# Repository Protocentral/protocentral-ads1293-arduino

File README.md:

# ProtoCentral ADS1293 ECG Arduino Library

Arduino library for the **ProtoCentral ADS1293 Breakout**: 3-lead and 5-lead ECG from the TI ADS1293 three-channel 24-bit analog front end. It exposes every feature of the chip, from lead-off detection and pace channels to the Wilson terminal and battery monitor, and runs on an Arduino Uno.

## Don't have one? [Buy it here](https://protocentral.com/product/protocentral-ads1293-breakout-board/)

## Links

| | |
|---|---|
| Product page | https://protocentral.com/product/protocentral-ads1293-breakout-board/ |
| Getting started guide (pinout, electrodes, OpenView) | https://protocentral.com/product/protocentral-ads1293-breakout-board/docs/getting-started/ |
| Hardware design files | https://github.com/Protocentral/protocentral_ads1293 |
| OpenView companion app | https://github.com/Protocentral/protocentral_openview |
| ADS1293 datasheet (TI SNAS602C) | https://www.ti.com/lit/ds/symlink/ads1293.pdf |

## How it works

The ADS1293 has three measurement channels, each with an instrumentation amplifier (fixed gain 3.5), a sigma-delta modulator and a digital filter. A switch matrix connects any of its six inputs to any channel. The library's lead sets use the breakout's electrode wiring:

| Channel | 3-lead | 5-lead |
|---|---|---|
| **CH1** | Lead I = LA − RA | Lead I = LA − RA |
| **CH2** | Lead II = LL − RA | Lead II = LL − RA |
| **CH3** | off | V1 − WCT (Wilson central terminal, built on-chip from RA, LA and LL) |

The right-leg drive holds the body at mid-supply through the RL electrode and cancels common-mode noise. Lead III = II − I.

## Features

- 3-lead and 5-lead ECG at 25–1600 SPS (up to 6.4 kSPS per channel), with any input-to-channel routing
- Lead-off detection: DC, analog AC and digital AC
- Digital pace data at up to 25.6 kSPS, and the analog pace channel
- Self-test signals, supply-voltage monitor and every error register
- Multi-board operation with a shared clock and SYNCB
- Polled, interrupt-driven, or no DRDY pin at all; readings converted to µV
- No dependencies. Runs on AVR, Uno R4, Nano 33 BLE, nRF52840, ESP32 (also S2/S3/C3) and RP2040

> **Not a medical device. For research and education only.** The breakout has no patient isolation: power the host from a battery when electrodes are on a person.

## Installation

- **Arduino Library Manager (recommended):** search for **ProtoCentral ADS1293** and install **ProtoCentral ADS1293 ECG Library**.
- **Manual:** download this repository as a ZIP, then use **Sketch → Include Library → Add .ZIP Library…**

## Wiring

The board pinout, electrode placement and power options are in the [getting started guide](https://protocentral.com/product/protocentral-ads1293-breakout-board/docs/getting-started/). The examples use each board's default SPI pins (SCK, MISO, MOSI) plus these:

| Breakout | Uno / Nano / R4 | ESP32 | ESP32-S2 / S3 | ESP32-C3 |
|---|---|---|---|---|
| CSB  | D4 | GPIO5 (SS) | SS (GPIO10 on S3) | GPIO7 (SS) |
| DRDY | D2 | GPIO4  | GPIO4 | GPIO3 |
| RST  | D5 | GPIO25 | GPIO5 | GPIO1 |
| SYNC | D6 | GPIO26 | GPIO6 | GPIO10 |

**Wire RST and SYNC to the MCU.** On the v2 board they reach the chip through a level shifter, with no pull-up on the header side. Connect both to MCU pins and pass those pins to the constructor; the library then holds them in a defined state. An RST or SYNC pin that is left undriven can stop conversions. (v1 boards have no SYNC pin: pass `-1` for it.)

Power the board from your MCU's I/O voltage: the header's logic level equals VCC.

## Quick Start

```cpp
#include <SPI.h>
#include "Protocentral_ADS1293.h"

Protocentral_ADS1293 ads(4 /*CS*/, 2 /*DRDY*/, 5 /*RST*/, 6 /*SYNC*/);

void setup() {
    Serial.begin(115200);
    if (!ads.begin()) {                        // 3-lead ECG at 200 SPS
        Serial.println((int)ads.lastError());  // see ADS1293_Status
        while (1);
    }
}

void loop() {
    ADS1293_Sample s;
    if (ads.available() && ads.read(s)) {
        Serial.print(ads.countsToMicrovolts(s.ecg[0]));  // Lead I, µV
        Serial.print(' ');
        Serial.println(ads.countsToMicrovolts(s.ecg[1], ADS1293_Channel::CH2));  // Lead II
    }
}
```

### Configuration

`begin()` with no arguments sets up 3-lead ECG at 200 SPS from the on-board crystal, with right-leg drive and DC lead-off detection. Pass an `ADS1293_Config` to change it:

```cpp
ADS1293_Config cfg;
cfg.leadSet  = ADS1293_LeadSet::FiveLead;   // ThreeLead, FiveLead or Custom
cfg.dataRate = ADS1293_DataRate::SPS_400;   // SPS_25 ... SPS_1600
cfg.leadOff  = false;
cfg.sync     = ADS1293_SyncMode::Auto;      // Master / Slave for multi-board sync
ads.begin(cfg);
```

The other fields (clock source, high-resolution mode, test signal, ...) are documented in `Protocentral_ADS1293.h`. Every setter also works later, while streaming.

Any `SPIClass` and any pin can be used: `Protocentral_ADS1293 ads(CS, DRDY, RST, SYNC, SPI1);`, with `-1` for pins that are not wired. On ESP32, `ads.begin(sck, miso, mosi)` selects custom SPI pins.

## Data format

`read()` fills an `ADS1293_Sample`:

| Field | Meaning |
|---|---|
| `ecg[3]` | ECG counts per channel, signed around mid-scale (0 = 0 V differential) |
| `pace[3]` | Pace counts (channels with pace read-back only) |
| `ecgUpdated` / `paceUpdated` | Bit *n* set: channel *n*+1 has a new conversion |
| `leadOff` | Lead-off flags (`ADS1293_ELECTRODE_RA` …), read while an alarm is active |
| `errors` | Error flags (`ADS1293_ERR_*`), read while an alarm is active |

`countsToMicrovolts(counts, channel)` converts to µV at the electrodes, using the full-scale code for the channel's current filter settings. The input range is ±400 mV differential.

## API Reference

| Method | Description |
|---|---|
| `Protocentral_ADS1293(cs, drdy = -1, reset = -1, sync = -1, SPIClass& spi = SPI)` | `-1` = pin not wired |
| `bool begin()` / `begin(const ADS1293_Config&)` | Reset, check the chip, configure, start and verify conversions |
| `ADS1293_Status lastError()` | `Ok`, `SpiError`, `WrongChipId`, `VerifyFailed`, `NoClock`, `Timeout`, ... |
| `bool available()` / `bool read(ADS1293_Sample&)` | New data is waiting / read it |
| `enableDataReadyInterrupt()` / `missedSamples()` | Latch DRDY with an interrupt / count overwritten samples |
| `dataReadyPinFault()` | True when DRDY did not follow the chip and the driver switched to polling |
| `reset()` / `end()` | Reset and re-apply the configuration / power down |
| `float countsToMicrovolts(counts, ch)` | Units |

The full feature API, grouped as in `Protocentral_ADS1293.h`, where each method is documented:

| Area | Methods |
|---|---|
| Conversion and power | `start`, `stop`, `standby`, `powerDown`, `wakeup` |
| Data rate and filters | `setDataRate`, `setR2`, `setR3`, `setDoublePaceRate`, `setHighSampleClock`, `setEcgFilterBypass`, `getSampleRate`, `getPaceRate` |
| Read-back and DRDY | `setEcgReadback`, `setPaceReadback`, `setDataReadySource`, `setDataReadyMasking` |
| Channels | `setChannelInputs`, `setChannelEnabled`, `setTestSignal`, `setHighResolution`, `setFaultDetection` |
| Lead-off | `configureLeadOffDC`, `configureLeadOffAnalogAC`, `configureLeadOffDigitalAC`, `disableLeadOff`, `readLeadOffStatus` |
| Patient reference | `configureCommonModeDetect`, `configureRLD`, `configureWilson`, `configureGoldberger`, `setReference` |
| Pace, clock, sync | `configureAnalogPace`, `setClockOutput`, `setSyncMode`, `configureSync`, `setDriveStrength` |
| Errors and monitoring | `readErrorStatus`, `readRangeErrors`, `readSyncErrors`, `readMiscErrors`, `setAlarmMask`, `setAlarmFilter`, `readSupplyVoltage` |
| Registers | `readRegister`, `writeRegister`, `printRegisters` |

## Examples

| # | Sketch | Description |
|---|---|---|
| 01 | `01.ThreeLeadSerialPlotter` | Leads I, II and III in µV in the Arduino Serial Plotter |
| 02 | `02.FiveLeadSerialPlotter` | Leads I, II and V1 (Wilson central terminal) |
| 03 | `03.OpenView` | Stream three leads to [OpenView](https://github.com/Protocentral/protocentral_openview) |
| 04 | `04.LeadOffDetection` | Report which electrode is off, DC or analog AC mode |
| 05 | `05.SelfTest` | Test signals and noise floor on all channels, no electrodes needed |
| 06 | `06.InterruptDriven` | 400 SPS with an interrupt on DRDY and a missed-sample counter |
| 07 | `07.PaceDetection` | 3.2 kSPS pace data and a simple pacemaker-pulse detector |
| 08 | `08.SupplyAndAlarms` | Supply voltage and every error register, decoded |
| 09 | `09.MultiBoardClockSync` | Two boards sharing clock and SYNCB: six ECG channels sampled in step |
| 10 | `10.Diagnostics` | Register dump plus clock, data-path, DRDY and signal-chain checks. **Run this first if something is wrong** |

All examples print at 115200 baud.

## Troubleshooting

Run `10.Diagnostics` first; it reports which stage fails.

- **`SpiError`:** check the CSB/SCK/MOSI/MISO wiring, VCC and GND. On ESP32-S2/S3/C3, do not use pins 18/19/23.
- **`VerifyFailed`:** registers do not read back correctly. Shorten the wires, or define `ADS1293_SPI_CLOCK 500000` before the include.
- **`NoClock`, or data that comes and goes between resets:** check that RST and SYNC are wired to the pins passed to the constructor (see Wiring), then power-cycle the board, not only the MCU.
- **DRDY stuck:** remove any pull-up or pull-down from DRDY. The library notices a DRDY pin that does not follow the chip and polls instead (`dataReadyPinFault()` returns true); `10.Diagnostics` reports it.

Electrode and signal-quality problems are covered in the [getting started guide](https://protocentral.com/product/protocentral-ads1293-breakout-board/docs/getting-started/).

## Migrating from 1.x

Version 2.0 is a ground-up rewrite; see [CHANGELOG.md](CHANGELOG.md).

| 1.x | 2.0 |
|---|---|
| `#include "protocentral_ads1293.h"` | `#include "Protocentral_ADS1293.h"` |
| `ads1293 ADS1293(DRDY, CS);` | `Protocentral_ADS1293 ads(CS, DRDY, RST, SYNC);` (note the order) |
| `begin()` + ten `configure…()` calls | `ads.begin()` or `ads.begin(cfg)`, which returns `bool` |
| `configureChannel3(...)` + `configureWilsonCentralTerminal()` | `cfg.leadSet = ADS1293_LeadSet::FiveLead` |
| `setSamplingRate(SamplingRate::SPS_128)` (actually 320 SPS) | `setDataRate(ADS1293_DataRate::SPS_320)` (names are the real rates) |
| `isDataReady()` + `getECGData()` | `if (ads.available() && ads.read(s))` |
| `samples.ch1` / `ch2` / `ch3` | `s.ecg[0]` / `s.ecg[1]` / `s.ecg[2]`, centred on 0 for 0 V input |
| `rawToVoltage(code)` | `ads.countsToMicrovolts(counts, channel)` |

## License

Software: MIT. See [LICENSE.md](LICENSE.md). Copyright (c) 2019-2026 ProtoCentral Electronics.

## Support

Open an issue on [GitHub](https://github.com/Protocentral/protocentral-ads1293-arduino/issues) or email support@protocentral.com.

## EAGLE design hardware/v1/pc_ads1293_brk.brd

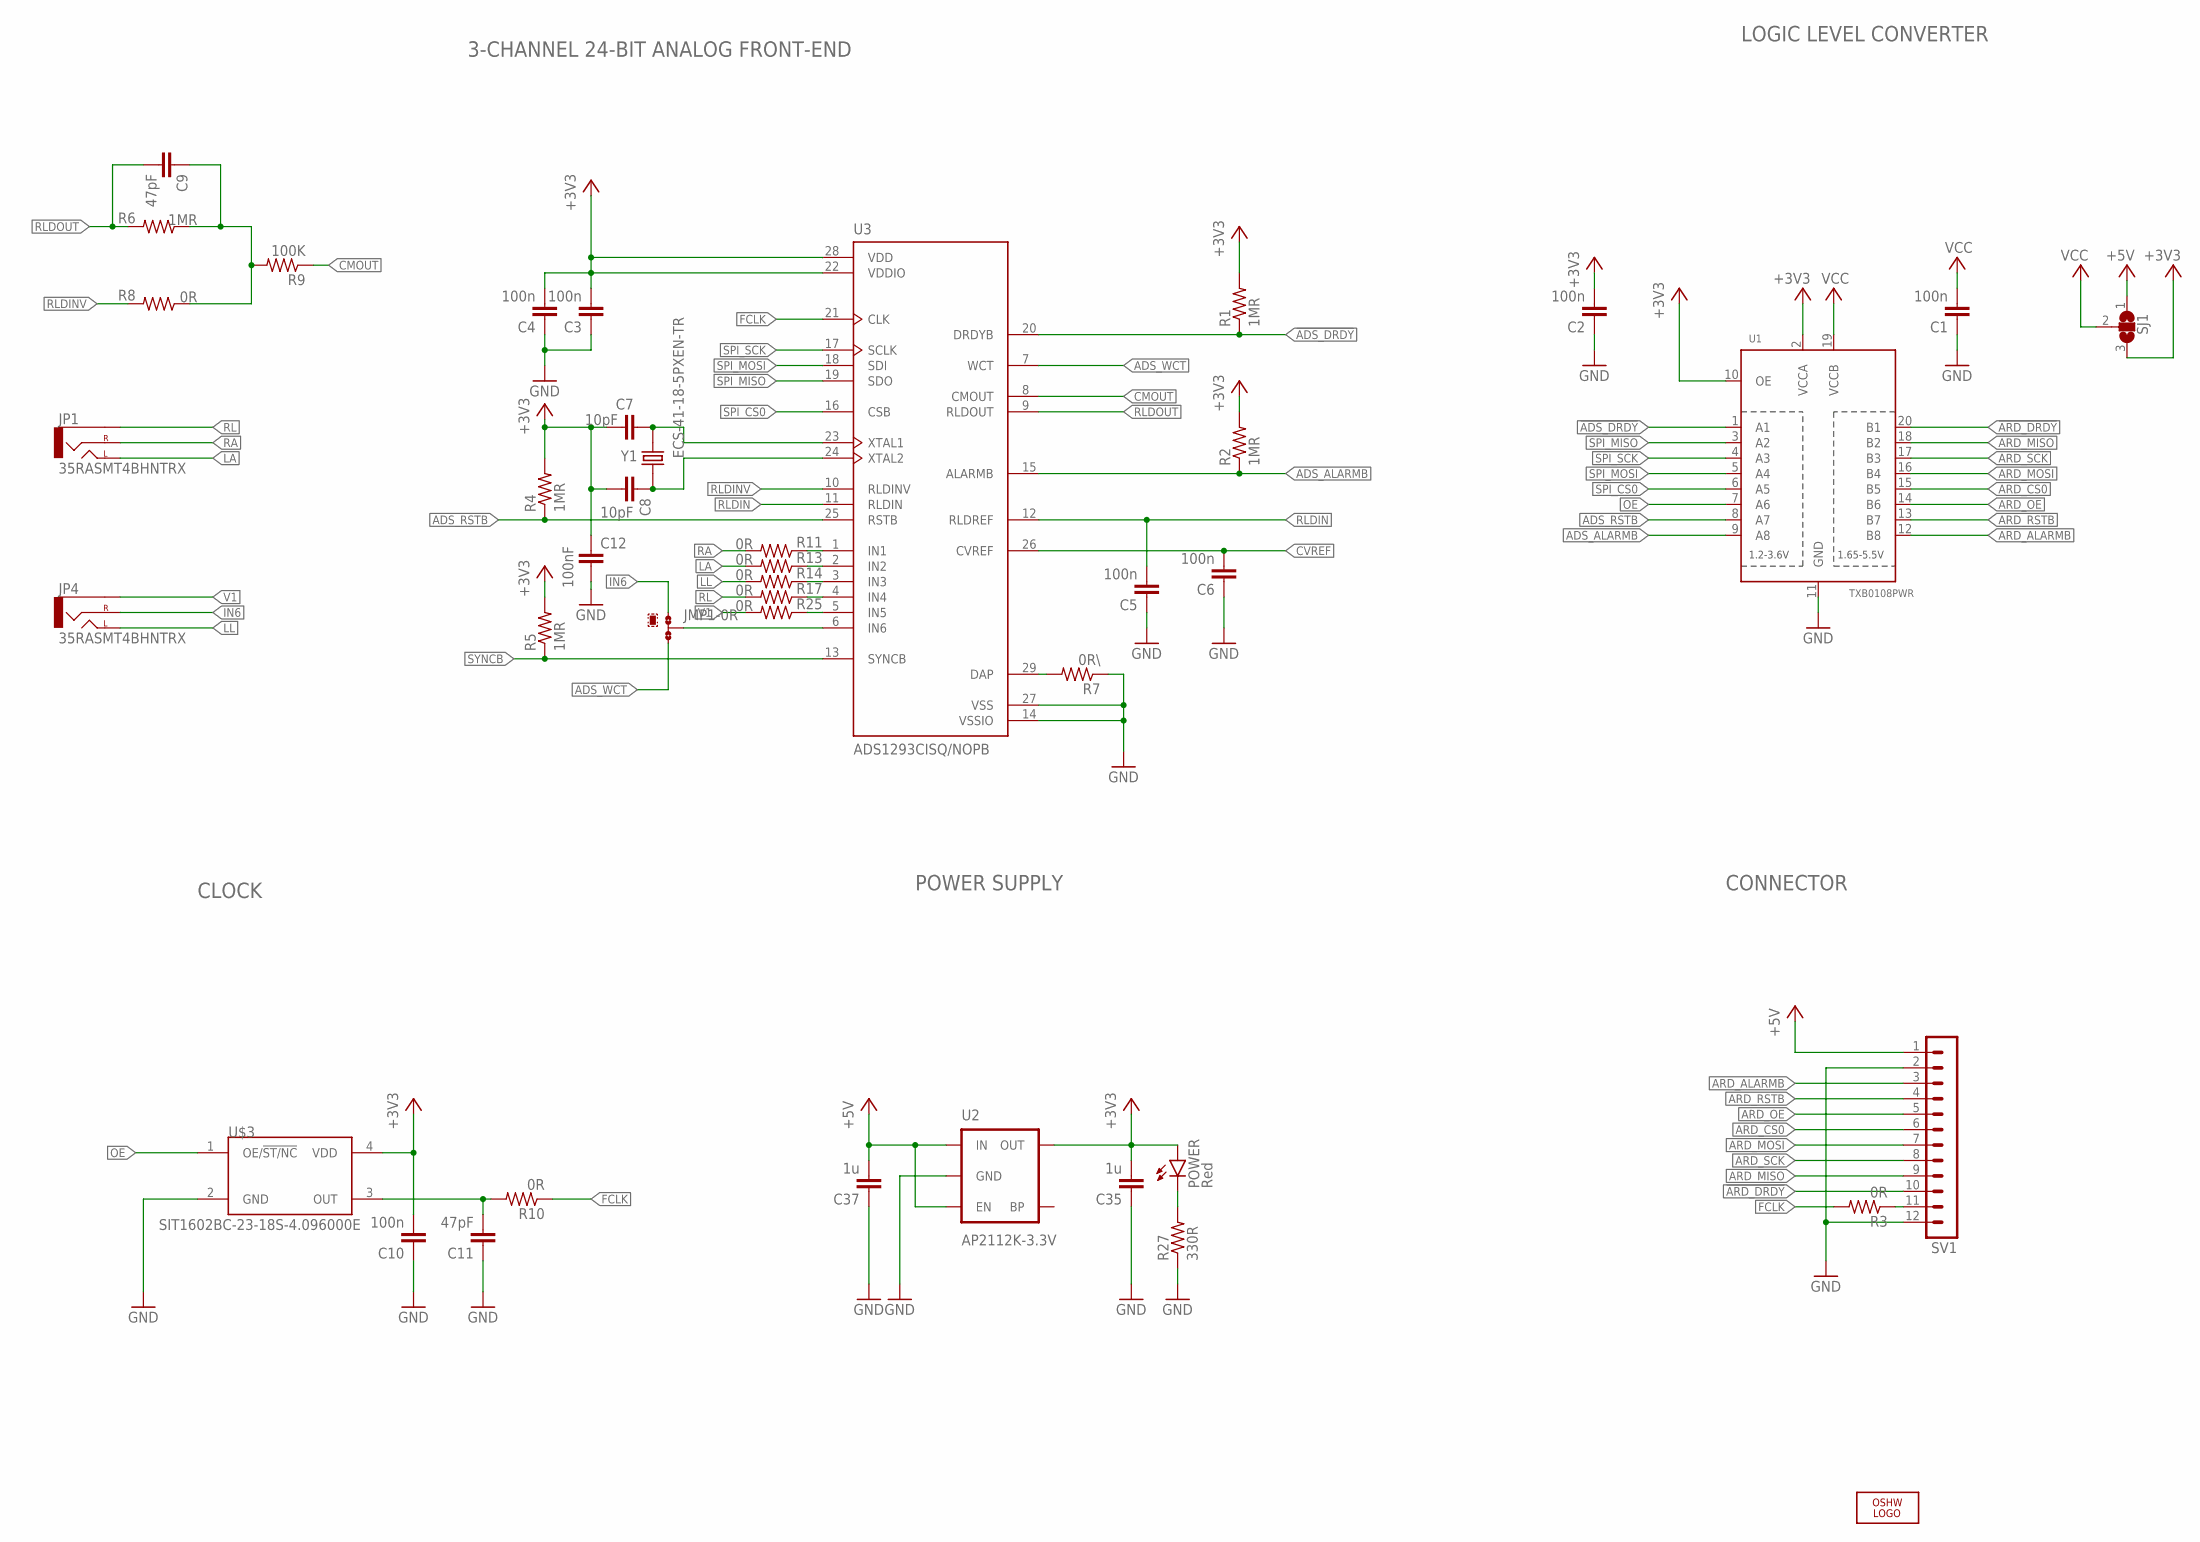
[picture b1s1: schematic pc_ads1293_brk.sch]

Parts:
C1, C2, C3, C4, C5, C6, C10: 100n; C0402
C7, C8: 10pF; C0402
C9, C11: 47pF; C0402
C12: 100nF; C0402
C35, C37: 1u; C0402
JMP1: 0R-JUMPB; B0R-JMP
JP1, JP4: 35RASMT4BHNTRX; AUDIO-JACK-3.5MM-SMD
LOGO1: OSHW_LOGO_FILLX0100-NT; OSHW_FILLX100_NOTEXT
POWER: Red; CHIPLED_0603
R1, R2, R4, R5, R6: 1MR; R0402
R3, R8, R10, R11, R13, R14, R17, R25: 0R; R0402
R7: 0R\; R0402
R9: 100K; R0402
R27: 330R; R0402
SJ1: SJ2W; SJ_2
SV1: MA12-1
U1: TXB0108PWR; TSSOP20
U2: AP2112K-3.3V; SOT23-5
U3: ADS1293CISQ/NOPB; QFN50P500X500X80-29N
U$3: SIT1602BC-23-18S-4.096000E; SIT1602B
Y1: ECS-41-18-5PXEN-TR; XTAL_ECS-41-18-5PXEN-TR

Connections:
!ADS_DRDY: R1.1, U1.1 (A1), U3.20 (DRDYB)
!ARD_DRDY: SV1.10, U1.20 (B1)
+3V3: C2.2, C3.2, C4.2, C7.2, C8.2, C10.2, C12.1, C35.2, POWER.A, R1.2, R2.2, R4.2, R5.2, SJ1.3, U1.2 (VCCA), U1.10 (OE), U2.5 (OUT), U3.22 (VDDIO), U3.28 (VDD), U$3.4 (VDD)
+5V: C37.2, SJ1.1, SV1.1, U2.1 (IN), U2.3 (EN)
ADS_ALARMB: R2.1, U1.9 (A8), U3.15 (ALARMB)
ADS_RSTB: R4.1, U1.8 (A7), U3.25 (RSTB)
ADS_WCT: JMP1.3, U3.7 (WCT)
ARD_ALARMB: SV1.3, U1.12 (B8)
ARD_CS0: SV1.6, U1.15 (B5)
ARD_MISO: SV1.9, U1.18 (B2)
ARD_MOSI: SV1.7, U1.16 (B4)
ARD_OE: SV1.5, U1.14 (B6)
ARD_RSTB: SV1.4, U1.13 (B7)
ARD_SCK: SV1.8, U1.17 (B3)
CLK: C11.2, R10.2, U$3.3 (OUT)
CMOUT: R9.1, U3.8 (CMOUT)
CVREF: C6.2, U3.26 (CVREF)
FCLK: R3.2, R10.1, U3.21 (CLK)
GND: C1.1, C2.1, C3.1, C4.1, C5.1, C6.1, C10.1, C11.1, C12.2, C35.1, C37.1, R7.1, R27.1, SV1.2, SV1.12, U1.11 (GND), U2.2 (GND), U3.14 (VSSIO), U3.27 (VSS), U$3.2 (GND)
IN6: JMP1.1, JP4.RING (RIGHT)
LA: JP1.TIP (LEFT), R13.2
LL: JP4.TIP (LEFT), R14.2
unnamed: C9.1, R6.1, R8.1, R9.2
unnamed: R11.1, U3.1 (IN1)
unnamed: JMP1.2, U3.6 (IN6)
unnamed: C8.1, U3.24 (XTAL2), Y1.1
unnamed: C7.1, U3.23 (XTAL1), Y1.2
unnamed: R13.1, U3.2 (IN2)
unnamed: POWER.C, R27.2
unnamed: R7.2, U3.29 (DAP)
unnamed: R14.1, U3.3 (IN3)
unnamed: R3.1, SV1.11
unnamed: R17.1, U3.4 (IN4)
unnamed: R25.1, U3.5 (IN5)
OE: U1.7 (A6), U$3.1 (OE/!ST/NC)
RA: JP1.RING (RIGHT), R11.2
RL: JP1.SLEEVE, R17.2
RLDIN: C5.2, U3.11 (RLDIN), U3.12 (RLDREF)
RLDINV: R8.2, U3.10 (RLDINV)
RLDOUT: C9.2, R6.2, U3.9 (RLDOUT)
SPI_CS0: U1.6 (A5), U3.16 (CSB)
SPI_MISO: U1.3 (A2), U3.19 (SDO)
SPI_MOSI: U1.5 (A4), U3.18 (SDI)
SPI_SCK: U1.4 (A3), U3.17 (SCLK)
SYNCB: R5.1, U3.13 (SYNCB)
V1: JP4.SLEEVE, R25.2
VCC: C1.2, SJ1.2, U1.19 (VCCB)

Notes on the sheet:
LOGIC LEVEL CONVERTER
CONNECTOR
POWER SUPPLY
CLOCK
3-CHANNEL 24-BIT ANALOG FRONT-END

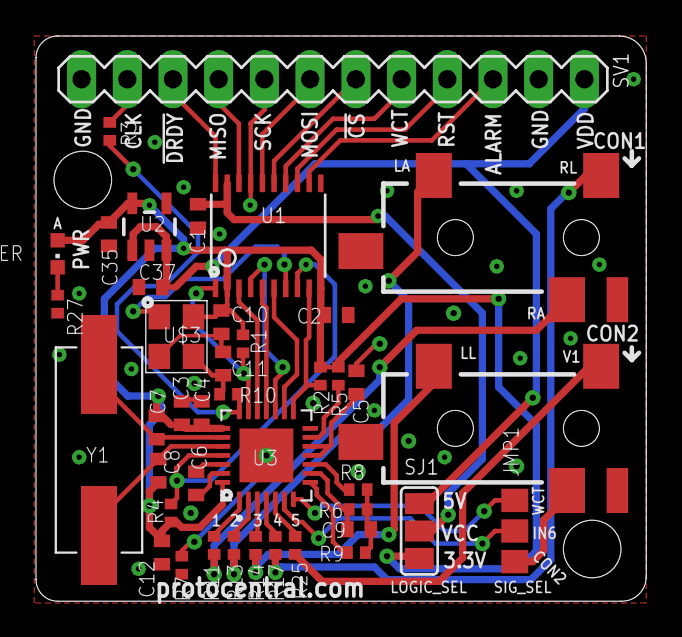
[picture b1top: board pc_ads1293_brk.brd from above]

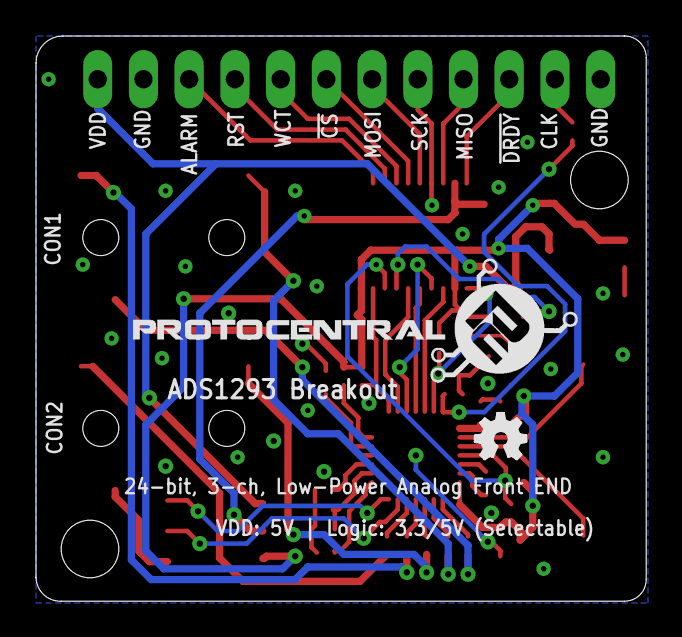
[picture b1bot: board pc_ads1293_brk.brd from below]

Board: 4 copper layers, 33.9 x 31.4 mm, 43 parts (2 on the bottom side), 47 nets.

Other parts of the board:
U$2: PROTY_WITH_TEXT

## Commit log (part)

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2020-12-15 added 5 channel configuration
2020-12-21 debug commit
2020-12-22 chnaged 3rd channel config
2020-12-23 fixed 3rd channel
2020-12-23 added supporting functions
2020-12-29 added example for openview GUI
2020-12-29 renamed examples
2024-12-10 updated readme, product images, library properties, keywords, schematic
2024-12-10 workflow added
2024-12-10 compilation error cleared
2025-03-04 complie-examples.yml updated
2025-03-04 actions/upload-artifact changed to v4
2025-03-04 artifact renamed
2025-03-04 yml file updated
2025-04-28 readme updated
2025-09-08 Working with high data rate
2025-09-08 Init commit
2025-09-10 Formatted an renamed all examples
2025-09-10 Formatting changes
2025-09-10 Change sampling rate function
2025-09-10 Bump version
2025-11-19 Corrected oscillator default setting
2025-12-19 Fix mux config issue
2025-12-19 Bump version. Update README
2026-05-27 Temp commit

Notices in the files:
parts and their libraries:
SparkFun-Connectors: Licensing: Creative Commons ShareAlike 4.0 International - https://creativecommons.org/licenses/by-sa/4.0
